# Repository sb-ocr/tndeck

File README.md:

# TN Deck

Watch the build video ↓

TN Deck is a tiny handheld cyberdeck built inside an Altoids tin around the Raspberry Pi Compute Module 0. Inspired by projects like the MintyPi and other tin-based builds, it uses custom PCBs, an integrated keyboard, a small display, onboard audio, and battery power.

<sub>⚠️ In these files, R23 was changed to 2.2kΩ to fix the soft-latch issue, and C33 was added to help reset the audio DAC on power-up.</sub>

[![CC BY-NC-SA 4.0][cc-by-nc-sa-shield]][cc-by-nc-sa]

[![CC BY-NC-SA 4.0][cc-by-nc-sa-image]][cc-by-nc-sa]

[cc-by-nc-sa]: http://creativecommons.org/licenses/by-nc-sa/4.0/
[cc-by-nc-sa-image]: https://licensebuttons.net/l/by-nc-sa/4.0/88x31.png
[cc-by-nc-sa-shield]: https://img.shields.io/badge/License-CC%20BY--NC--SA%204.0-lightgrey.svg

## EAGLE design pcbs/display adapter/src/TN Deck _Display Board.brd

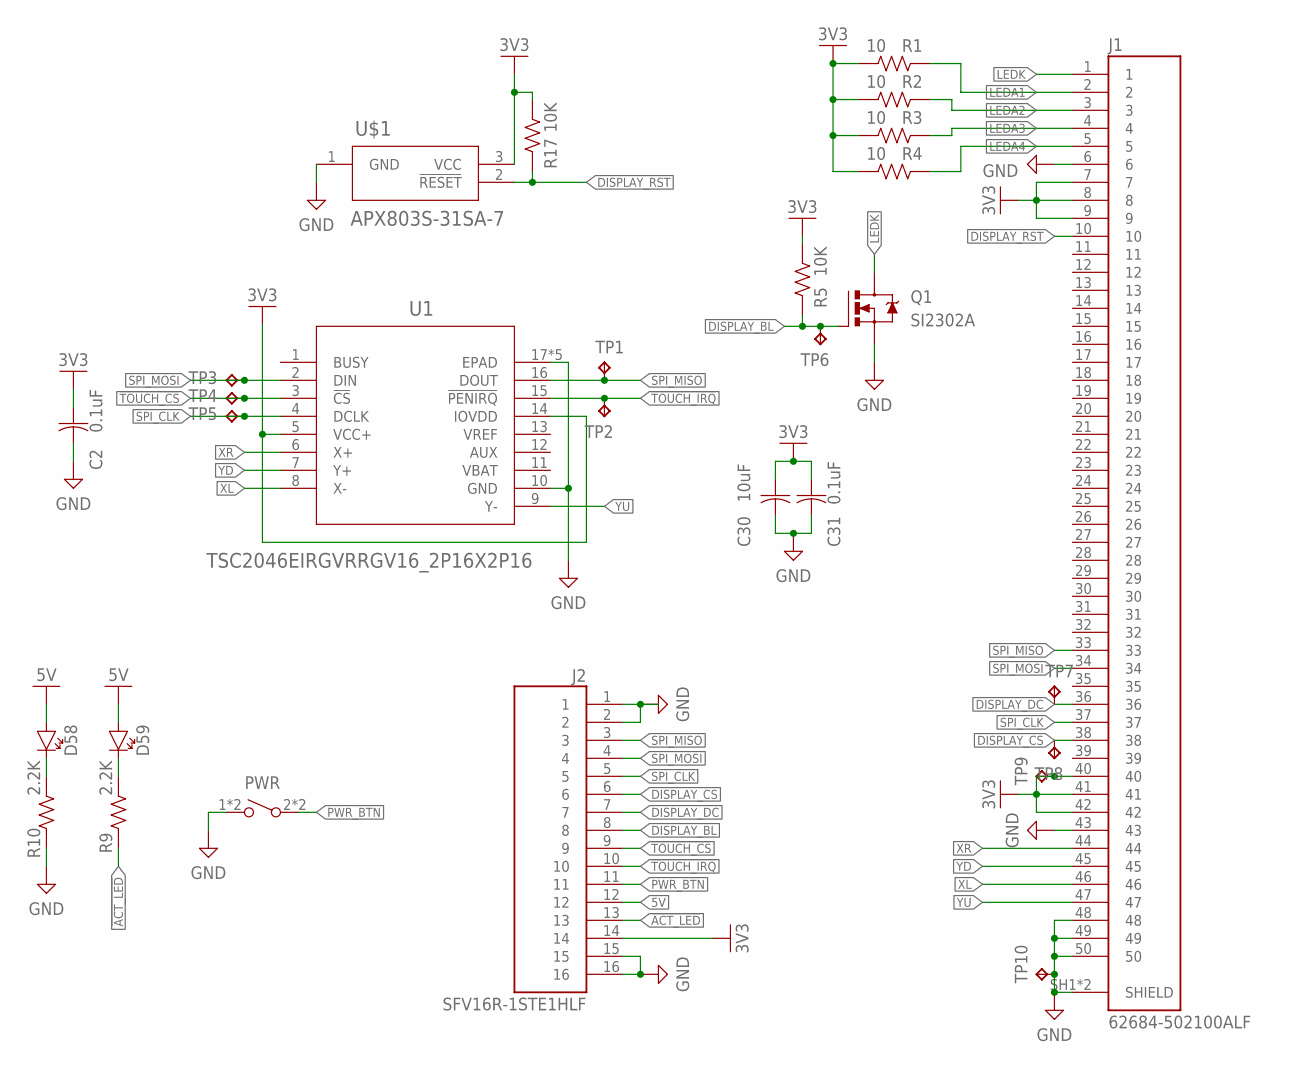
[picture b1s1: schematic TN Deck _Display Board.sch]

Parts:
C2, C31: 0.1uF; CAPC1608X85
C30: 10uF; CAPC2012X110
D58, D59: CHIP-FLAT-G_0603-0.80MM; LEDC1608X80N_FLAT-G
J1: 62684-502100ALF; AMPHENOL_62684-502100ALF
J2: SFV16R-1STE1HLF; AMPHENOL_SFV16R-1STE1HLF
PWR: SPST-NO_SWITCH_KMR2; KMR2
Q1: SI2302A; SOT23
R1, R2, R3, R4: 10; RESC1608X60
R5, R17: 10K; RESC1608X60
R9, R10: 2.2K; RESC1608X60
TP1, TP2, TP3, TP4, TP5, TP6, TP7, TP8, TP9, TP10: TPB1,27; B1,27
U1: TSC2046EIRGVRRGV16_2P16X2P16; RGV16_2P16X2P16
U$1: APX803S-31SA-7; SOT-23_DIO

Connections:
3V3: C2.1, C30.1, C31.1, J1.7, J1.8, J1.9, J1.40, J1.41, J1.42, J2.14, R1.2, R2.2, R3.2, R4.2, R5.2, R17.2, TP9.TP, U1.5 (VCC+), U1.14 (IOVDD), U$1.3 (VCC)
5V: D58.A, D59.A, J2.12
!ACT_LED: J2.13, R9.1
!TOUCH_CS: J2.9, TP4.TP, U1.3 (!CS)
!TOUCH_IRQ: J2.10, TP2.TP, U1.15 (!PENIRQ)
DISPLAY_BL: J2.8, Q1.1 (G), R5.1, TP6.TP
DISPLAY_CS: J1.38, J2.6, TP8.TP
DISPLAY_DC: J1.36, J2.7, TP7.TP
DISPLAY_RST: J1.10, R17.1, U$1.2 (!RESET)
GND: C2.2, C30.2, C31.2, J1.6, J1.43, J1.48, J1.49, J1.50, J1.SH1 (SHIELD), J1.SH2 (SHIELD), J2.1, J2.2, J2.15, J2.16, PWR.1, PWR.4 (1), Q1.2 (S), R10.1, TP10.TP, U1.10 (GND), U1.17 (EPAD), U1.V (EPAD), U1.V_1 (EPAD), U1.V_2 (EPAD), U1.V_3 (EPAD), U$1.1 (GND)
LEDA1: J1.2, R1.1
LEDA2: J1.3, R2.1
LEDA3: J1.4, R3.1
LEDA4: J1.5, R4.1
LEDK: J1.1, Q1.3 (D)
unnamed: D59.C, R9.2
unnamed: D58.C, R10.2
PWR_BTN: J2.11, PWR.2, PWR.3 (2)
SPI_CLK: J1.37, J2.5, TP5.TP, U1.4 (DCLK)
SPI_MISO: J1.33, J2.3, TP1.TP, U1.16 (DOUT)
SPI_MOSI: J1.34, J2.4, TP3.TP, U1.2 (DIN)
VREF: U1.13 (VREF)
XL: J1.46, U1.8 (X-)
XR: J1.44, U1.6 (X+)
YD: J1.45, U1.7 (Y+)
YU: J1.47, U1.9 (Y-)

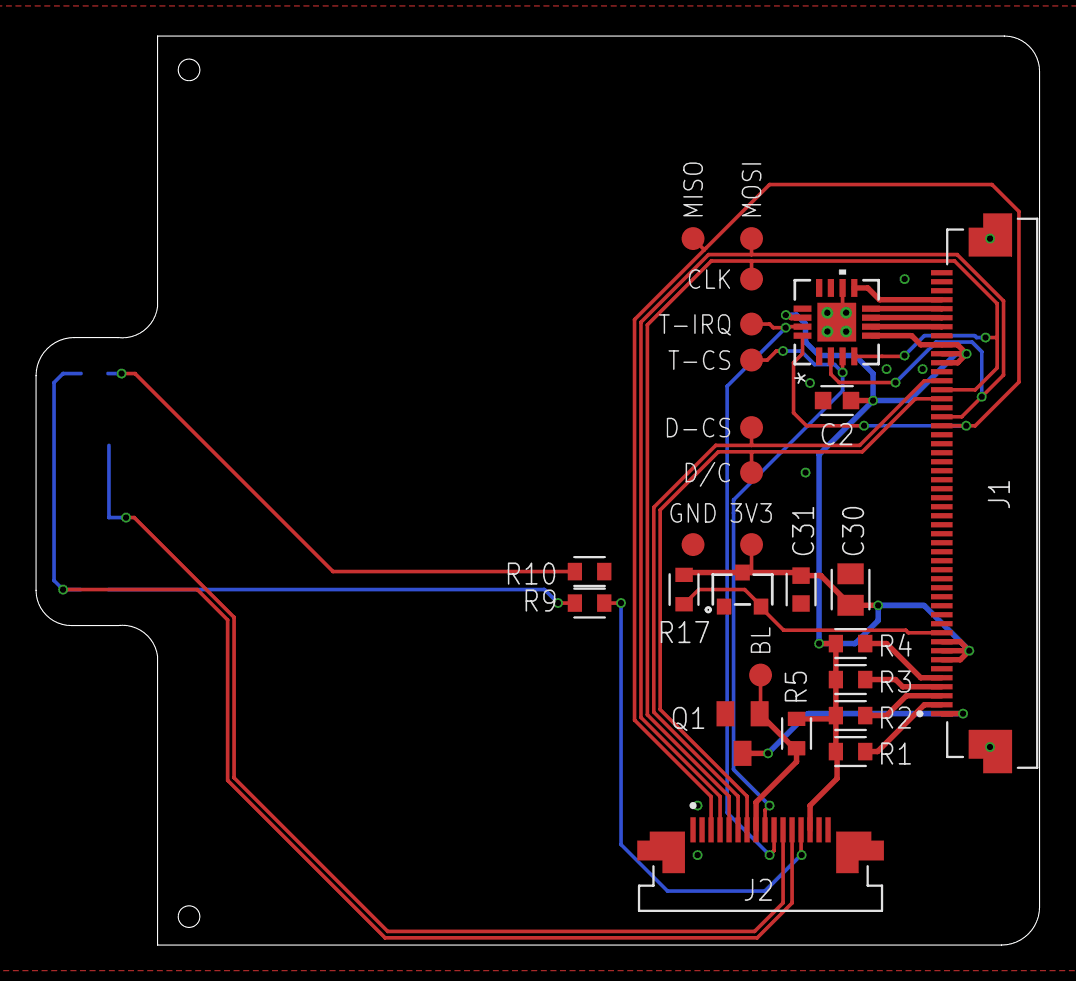
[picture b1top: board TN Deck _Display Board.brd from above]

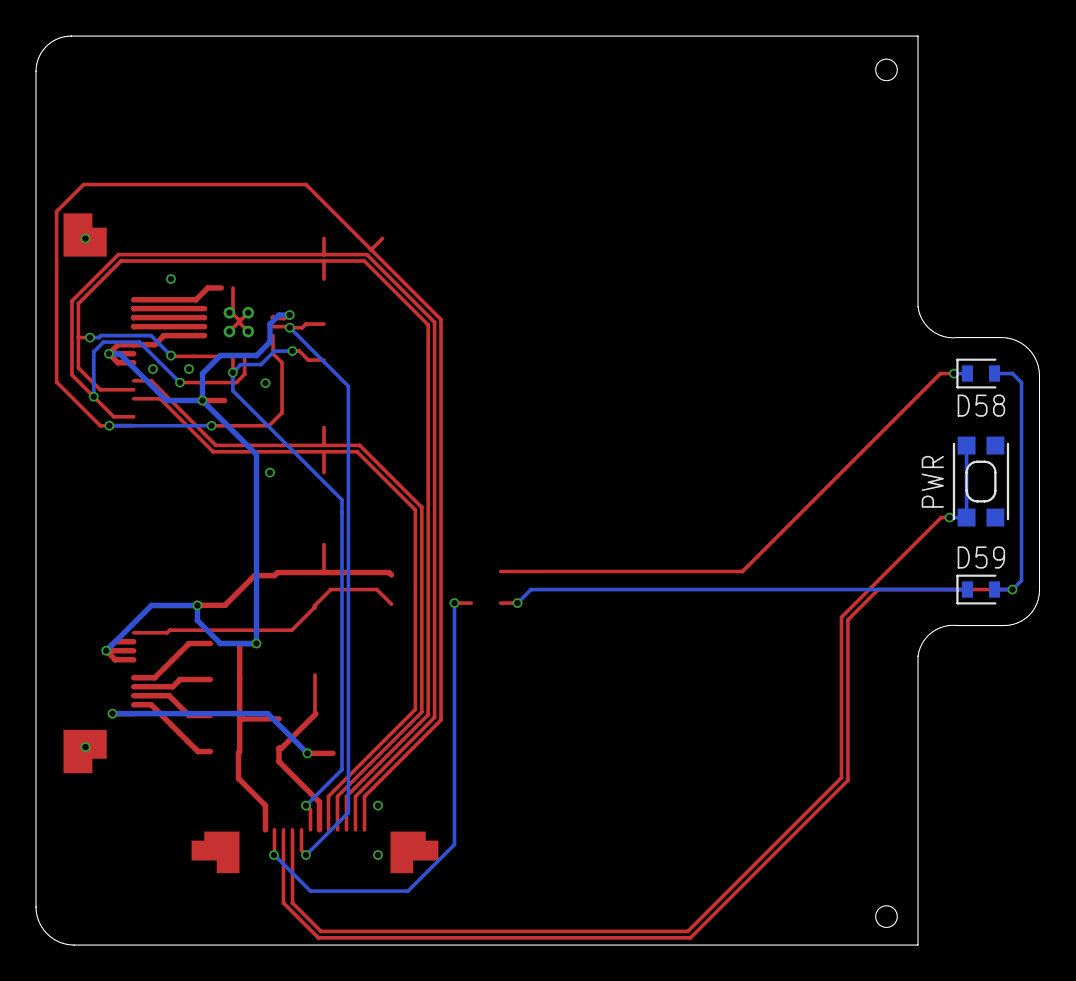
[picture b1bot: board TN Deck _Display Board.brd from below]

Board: 2 copper layers, 55.7 x 50.5 mm, 29 parts (3 on the bottom side), 25 nets.

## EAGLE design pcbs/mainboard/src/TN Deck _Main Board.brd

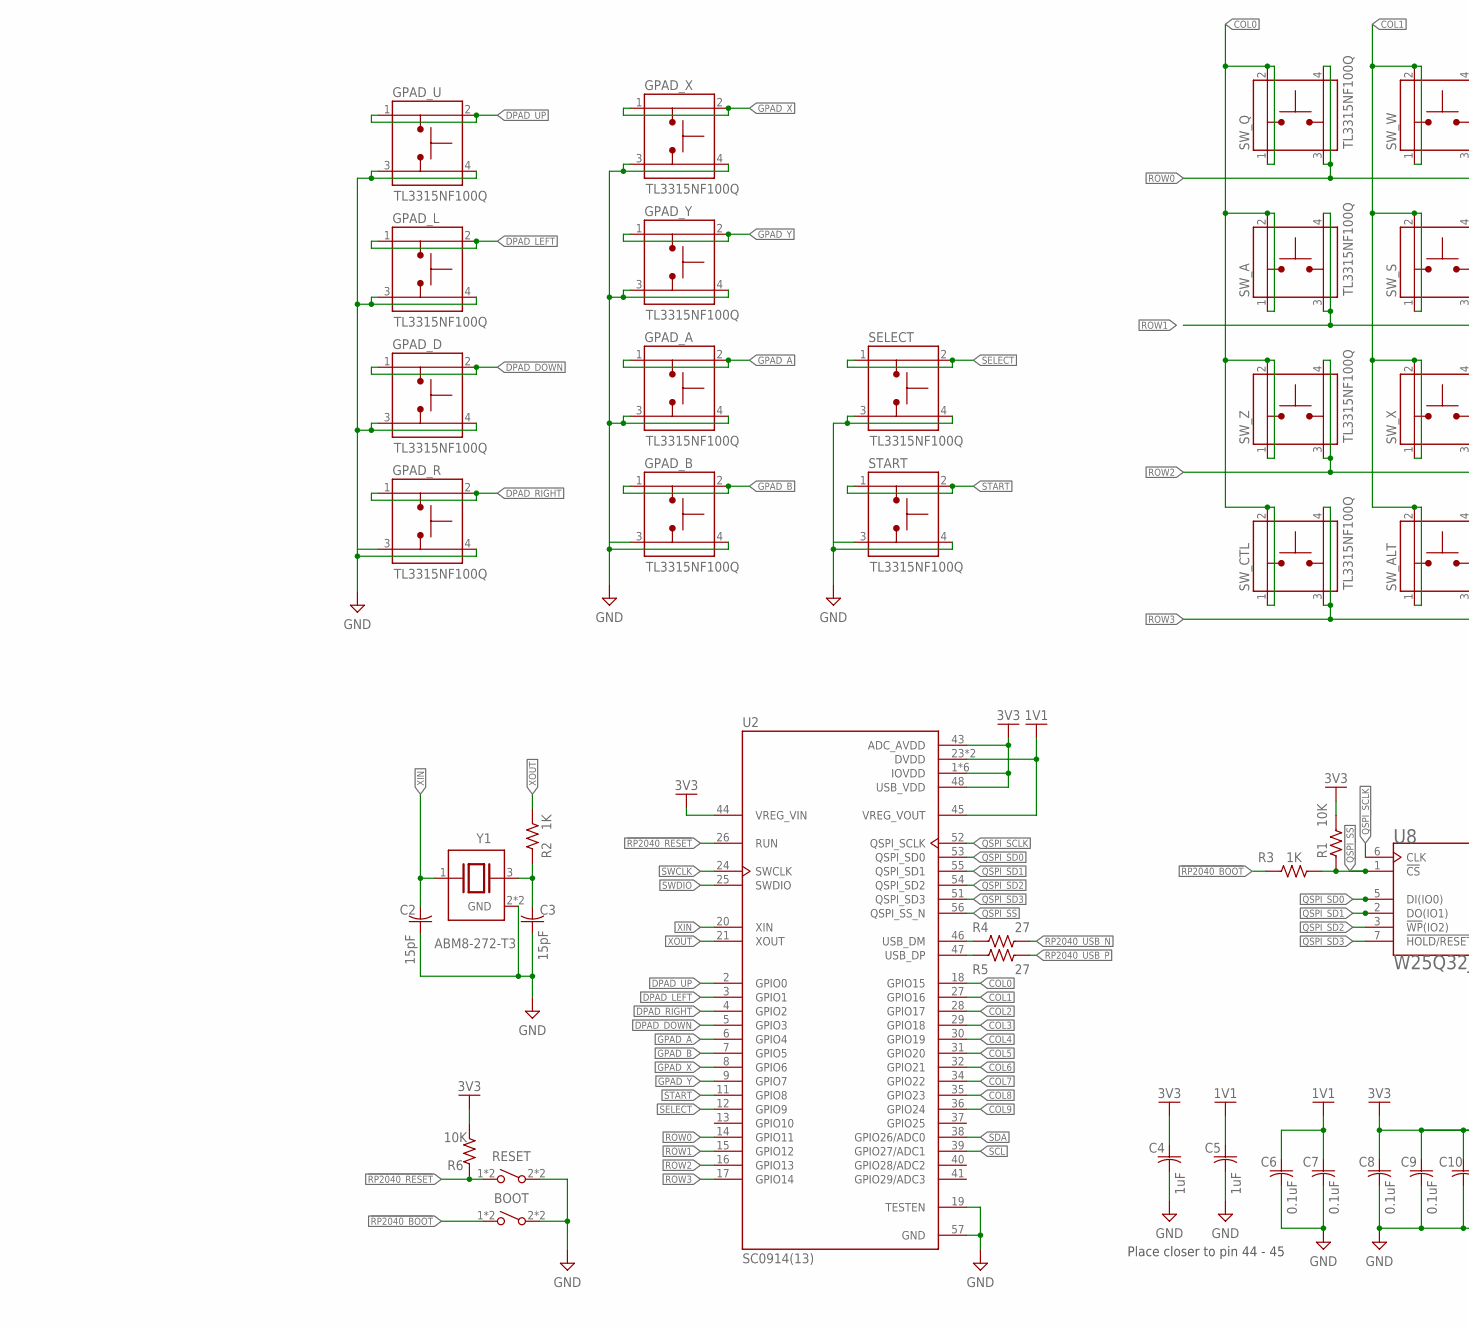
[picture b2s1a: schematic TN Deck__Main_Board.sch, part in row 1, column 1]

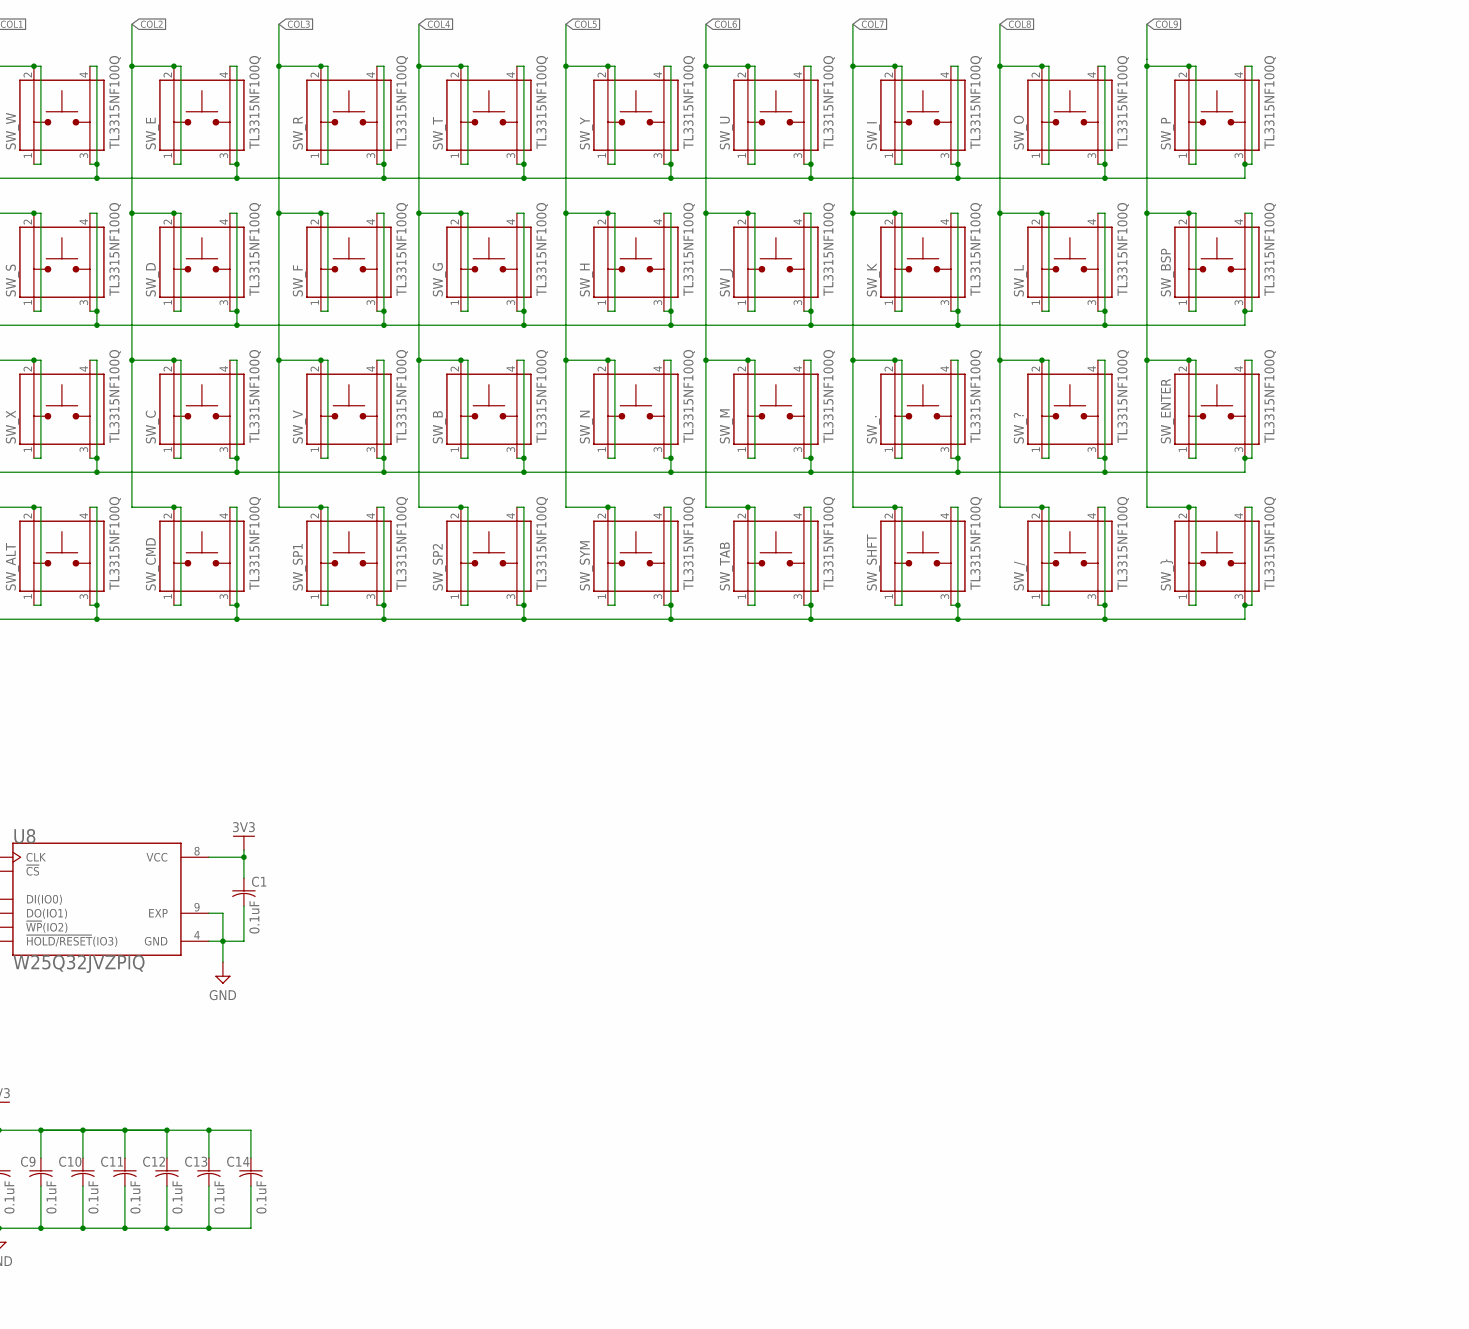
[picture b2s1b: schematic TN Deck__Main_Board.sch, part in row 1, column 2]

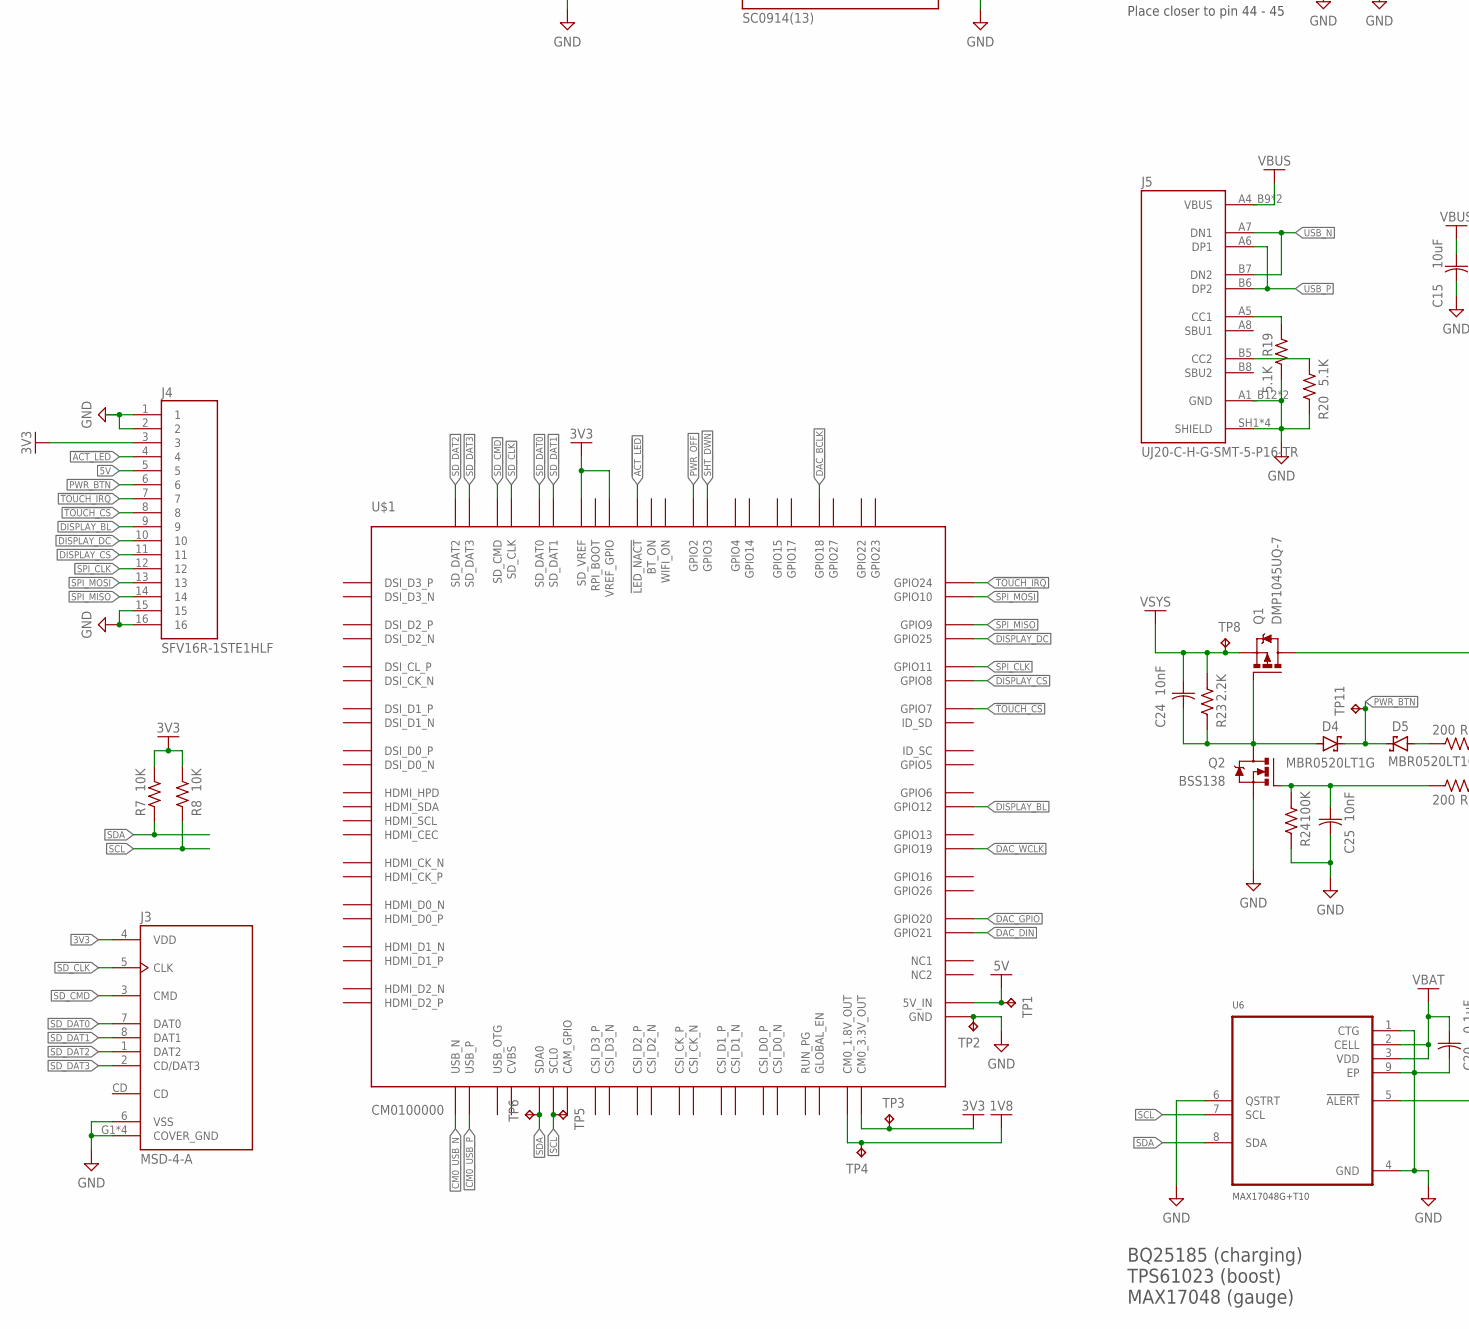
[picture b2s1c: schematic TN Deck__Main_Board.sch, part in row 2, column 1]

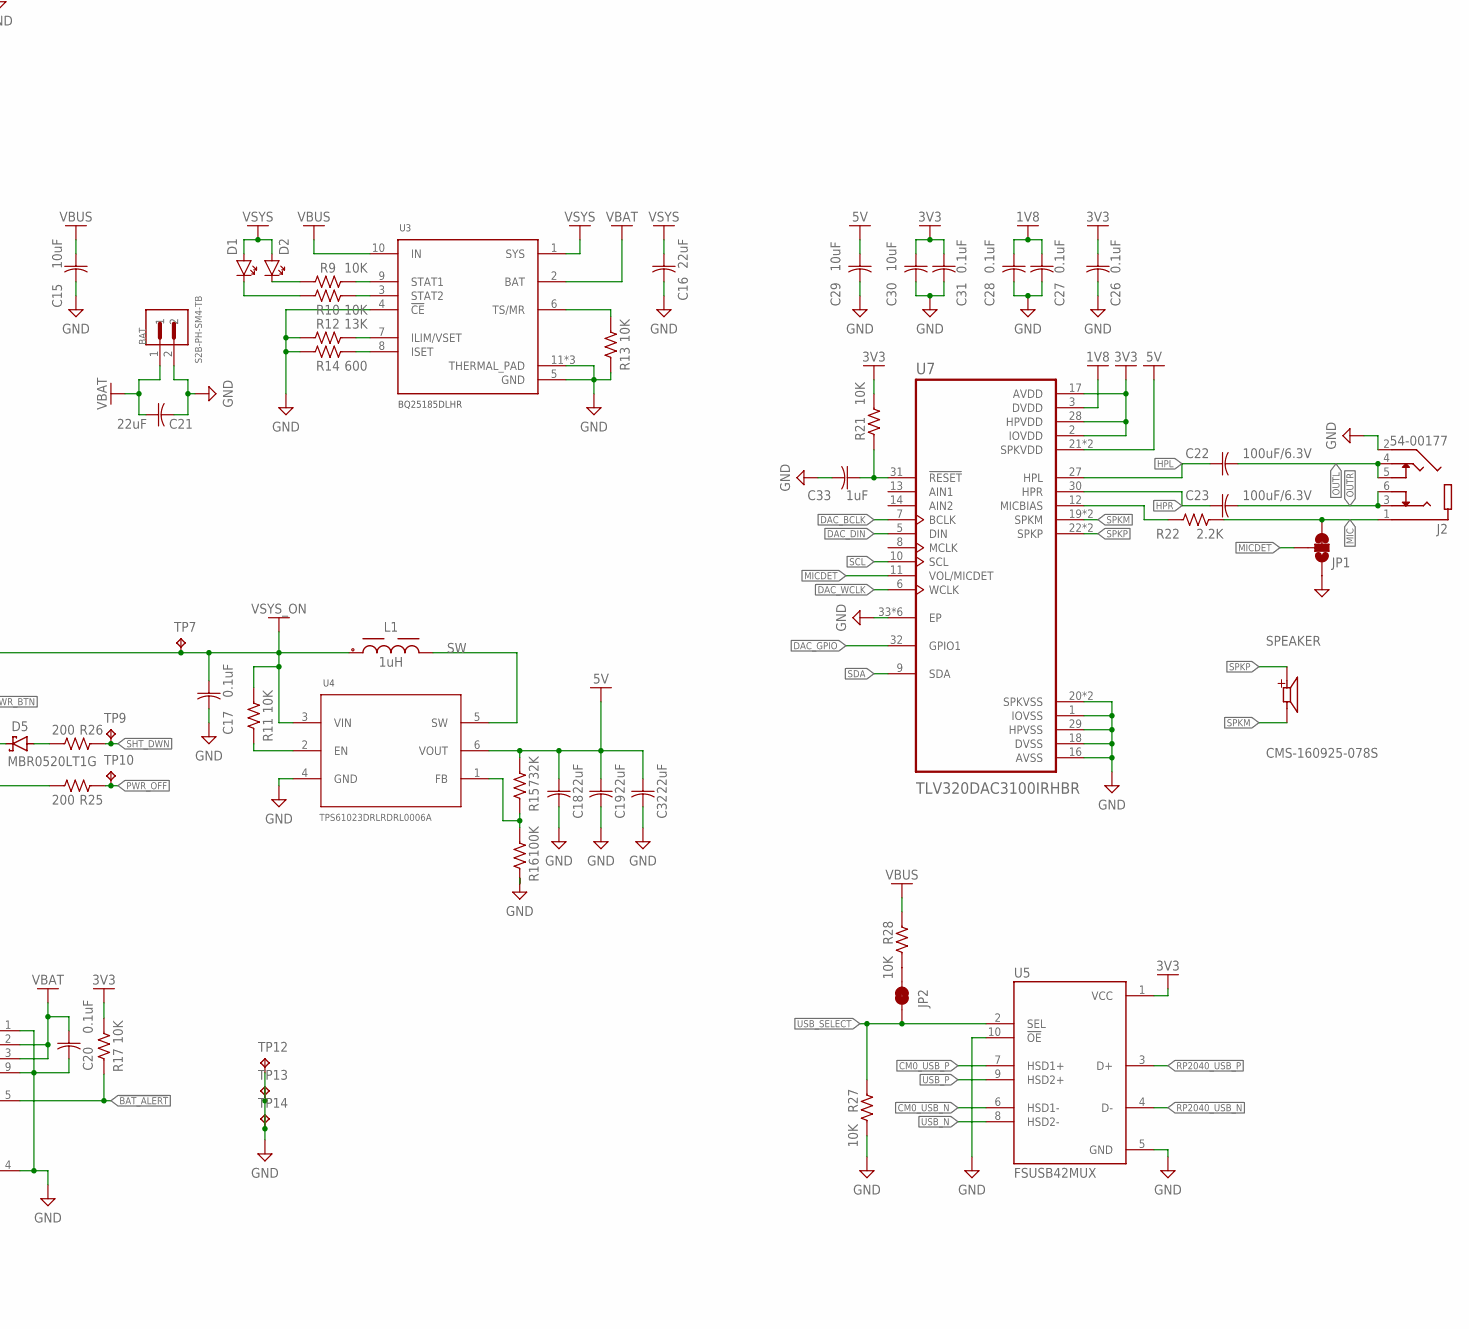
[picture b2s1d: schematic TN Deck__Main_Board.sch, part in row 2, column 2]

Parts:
BAT: S2B-PH-SM4-TB; JST_S2B-PH-SM4-TB
BOOT: SPST-NO_SWITCH_KMR2; KMR2
C1, C6, C7, C8, C9, C10, C11, C12, C13, C14, C17, C20, C26, C27, C28, C31: 0.1uF; CAPC1608X85
C2, C3: 15pF; CAPC1608X85
C4, C5, C33: 1uF; CAPC1608X85
C15, C29, C30: 10uF; CAPC2012X110
C16, C18, C19, C21, C32: 22uF; CAPC2012X110
C22, C23: 100uF/6.3V; CAPC3216X135
C24, C25: 10nF; CAPC1608X85
D1: CHIP-FLAT-G_0603-0.80MM; LEDC1608X80N_FLAT-G
D2: CHIP-FLAT-R_0603-0.80MM; LEDC1608X80N_FLAT-R
D4, D5: MBR0520LT1G; SODFL3718X115
GPAD_A: TL3315NF100Q
GPAD_B: TL3315NF100Q
GPAD_D: TL3315NF100Q
GPAD_L: TL3315NF100Q
GPAD_R: TL3315NF100Q
GPAD_U: TL3315NF100Q
GPAD_X: TL3315NF100Q
GPAD_Y: TL3315NF100Q
J2: 54-00177; TENSILITY_54-00177
J3: MSD-4-A; CUI_MSD-4-A
J4: SFV16R-1STE1HLF; AMPHENOL_SFV16R-1STE1HLF
J5: UJ20-C-H-G-SMT-5-P16-TR; SAMESKY_UJ20-C-H-G-SMT-5-P16-TR
JP1: JUMPER-SMT_3_1-NC_TRACE_SILK; SMT-JUMPER_3_1-NC_TRACE_SILK
JP2: JUMPER-SMT_2_NC_TRACE_NO-SILK; SMT-JUMPER_2_NC_TRACE_NO-SILK
L1: 1uH; WE-XHMI_4020
Q1: DMP1045UQ-7; SOT23
Q2: BSS138; SOT23
R1, R6, R7, R8, R9, R10, R11, R13, R17, R21, R27, R28: 10K; RESC1608X60
R2, R3: 1K; RESC1608X60
R4, R5: 27; RESC1608X60
R12: 13K; RESC1608X60
R14: 600; RESC1608X60
R15: 732K; RESC1608X60
R16, R24: 100K; RESC1608X60
R19, R20: 5.1K; RESC1608X60
R22, R23: 2.2K; RESC1608X60
R25, R26: 200; RESC1608X60
RESET: SPST-NO_SWITCH_KMR2; KMR2
SELECT: TL3315NF100Q
SPEAKER: CMS-160925-078S; SPKR_CMS-160925-078S
START: TL3315NF100Q
SW_.: TL3315NF100Q
SW_/: TL3315NF100Q
SW_?: TL3315NF100Q
SW_A: TL3315NF100Q
SW_ALT: TL3315NF100Q
SW_B: TL3315NF100Q
SW_BSP: TL3315NF100Q
SW_C: TL3315NF100Q
SW_CMD: TL3315NF100Q
SW_CTL: TL3315NF100Q
SW_D: TL3315NF100Q
SW_E: TL3315NF100Q
SW_ENTER: TL3315NF100Q
SW_F: TL3315NF100Q
SW_G: TL3315NF100Q
SW_H: TL3315NF100Q
SW_I: TL3315NF100Q
SW_J: TL3315NF100Q
SW_K: TL3315NF100Q
SW_L: TL3315NF100Q
SW_M: TL3315NF100Q
SW_N: TL3315NF100Q
SW_O: TL3315NF100Q
SW_P: TL3315NF100Q
SW_Q: TL3315NF100Q
SW_R: TL3315NF100Q
SW_S: TL3315NF100Q
SW_SHFT: TL3315NF100Q
SW_SP1, SW_SP2: TL3315NF100Q
SW_SYM: TL3315NF100Q
SW_T: TL3315NF100Q
SW_TAB: TL3315NF100Q
SW_U: TL3315NF100Q
SW_V: TL3315NF100Q
SW_W: TL3315NF100Q
SW_X: TL3315NF100Q
SW_Y: TL3315NF100Q
SW_Z: TL3315NF100Q
SW_}: TL3315NF100Q
TP1, TP2, TP3, TP4, TP5, TP6, TP7, TP8, TP9, TP10, TP11, TP12, TP13, TP14: TPB1,27; B1,27
U2: SC0914(13); QFN40P700X700X90-57N
U3: BQ25185DLHR; IC_BQ25185DLHR
U4: TPS61023DRLRDRL0006A; DRL0006A
U5: FSUSB42MUX; SOP50P490X110-10N
U6: MAX17048G+T10; SON50P200X200X80-9N
U7: TLV320DAC3100IRHBR; IC_ADS125H01IRHBT
U8: W25Q32JVZPIQ; SON127P600X500X80-9N
U$1: CM0100000; CM0
Y1: ABM8-272-T3; XTAL_ABM8-272-T3

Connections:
1V1: C5.1, C6.1, C7.1, U2.23 (DVDD), U2.45 (VREG_VOUT), U2.50 (DVDD)
1V8: C27.1, C28.1, TP4.TP, U7.3 (DVDD), U$1.P$64 (CM0_1.8V_OUT), U$1.P$65 (CM0_1.8V_OUT)
3V3: C1.1, C4.1, C8.1, C9.1, C10.1, C11.1, C12.1, C13.1, C14.1, C26.1, C30.1, C31.1, J3.4 (VDD), J4.3, R1.2, R6.2, R7.2, R8.2, R17.2, R21.2, TP3.TP, U2.1 (IOVDD), U2.10 (IOVDD), U2.22 (IOVDD), U2.33 (IOVDD), U2.42 (IOVDD), U2.43 (ADC_AVDD), U2.44 (VREG_VIN), U2.48 (USB_VDD), U2.49 (IOVDD), U5.1 (VCC), U7.2 (IOVDD), U7.17 (AVDD), U7.28 (HPVDD), U8.8 (VCC), U$1.P$41 (CM0_3.3V_OUT), U$1.P$119 (CM0_3.3V_OUT), U$1.P$120 (VREF_GPIO), U$1.P$122 (SD_VREF)
5V: C18.1, C19.1, C29.1, C32.1, J4.5, R15.2, TP1.TP, U4.6 (VOUT), U7.21 (SPKVDD), U7.24 (SPKVDD), U$1.P$67 (5V_IN), U$1.P$68 (5V_IN)
!ACT_LED: J4.4, U$1.P$118 (!LED_NACT)
!BAT_ALERT: R17.1, U6.5 (!ALERT)
!RP2040_BOOT: BOOT.1, BOOT.4 (1), R3.1
!RP2040_RESET: R6.1, RESET.1, RESET.4 (1), U2.26 (RUN)
!TOUCH_CS: J4.8, U$1.P$89 (GPIO7)
!TOUCH_IRQ: J4.7, U$1.P$98 (GPIO24)
CM0_USB_N: U5.6 (HSD1-), U$1.P$35 (USB_N)
CM0_USB_P: U5.7 (HSD1+), U$1.P$36 (USB_P)
COL0: SW_A.1, SW_A.2, SW_CTL.1, SW_CTL.2, SW_Q.1, SW_Q.2, SW_Z.1, SW_Z.2, U2.18 (GPIO15)
COL1: SW_ALT.1, SW_ALT.2, SW_S.1, SW_S.2, SW_W.1, SW_W.2, SW_X.1, SW_X.2, U2.27 (GPIO16)
COL2: SW_C.1, SW_C.2, SW_CMD.1, SW_CMD.2, SW_D.1, SW_D.2, SW_E.1, SW_E.2, U2.28 (GPIO17)
COL3: SW_F.1, SW_F.2, SW_R.1, SW_R.2, SW_SP1.1, SW_SP1.2, SW_V.1, SW_V.2, U2.29 (GPIO18)
COL4: SW_B.1, SW_B.2, SW_G.1, SW_G.2, SW_SP2.1, SW_SP2.2, SW_T.1, SW_T.2, U2.30 (GPIO19)
COL5: SW_H.1, SW_H.2, SW_N.1, SW_N.2, SW_SYM.1, SW_SYM.2, SW_Y.1, SW_Y.2, U2.31 (GPIO20)
COL6: SW_J.1, SW_J.2, SW_M.1, SW_M.2, SW_TAB.1, SW_TAB.2, SW_U.1, SW_U.2, U2.32 (GPIO21)
COL7: SW_..1, SW_..2, SW_I.1, SW_I.2, SW_K.1, SW_K.2, SW_SHFT.1, SW_SHFT.2, U2.34 (GPIO22)
COL8: SW_/.1, SW_/.2, SW_?.1, SW_?.2, SW_L.1, SW_L.2, SW_O.1, SW_O.2, U2.35 (GPIO23)
COL9: SW_BSP.1, SW_BSP.2, SW_ENTER.1, SW_ENTER.2, SW_P.1, SW_P.2, SW_}.1, SW_}.2, U2.36 (GPIO24)
DAC_BCLK: U7.7 (BCLK), U$1.P$105 (GPIO18)
DAC_DIN: U7.5 (DIN), U$1.P$73 (GPIO21)
DAC_GPIO: U7.32 (GPIO1), U$1.P$74 (GPIO20)
DAC_WCLK: U7.6 (WCLK), U$1.P$79 (GPIO19)
DISPLAY_BL: J4.9, U$1.P$82 (GPIO12)
DISPLAY_CS: J4.11, U$1.P$91 (GPIO8)
DISPLAY_DC: J4.10, U$1.P$94 (GPIO25)
DPAD_DOWN: GPAD_D.1, GPAD_D.2, U2.5 (GPIO3)
DPAD_LEFT: GPAD_L.1, GPAD_L.2, U2.3 (GPIO1)
DPAD_RIGHT: GPAD_R.1, GPAD_R.2, U2.4 (GPIO2)
DPAD_UP: GPAD_U.1, GPAD_U.2, U2.2 (GPIO0)
GND: BAT.2, BOOT.2, BOOT.3 (2), C1.2, C2.1, C3.1, C4.2, C5.2, C6.2, C7.2, C8.2, C9.2, C10.2, C11.2, C12.2, C13.2, C14.2, C15.2, C16.2, C17.2, C18.2, C19.2, C20.2, C21.2, C25.2, C26.2, C27.2, C28.2, C29.2, C30.2, C31.2, C32.2, C33.2, GPAD_A.3, GPAD_A.4, GPAD_B.3, GPAD_B.4, GPAD_D.3, GPAD_D.4, GPAD_L.3, GPAD_L.4, GPAD_R.3, GPAD_R.4, GPAD_U.3, GPAD_U.4, GPAD_X.3, GPAD_X.4, GPAD_Y.3, GPAD_Y.4, J2.2, J3.6 (VSS), J3.G1 (COVER_GND), J3.G2 (COVER_GND), J3.G3 (COVER_GND), J3.G4 (COVER_GND), J4.1, J4.2, J4.15, J4.16, J5.A1_B12 (GND), J5.A12_B1 (GND), J5.SH1 (SHIELD), J5.SH2 (SHIELD), J5.SH3 (SHIELD), J5.SH4 (SHIELD), JP1.1, Q2.2 (S), R12.1, R13.1, R14.1, R16.1, R19.2, R20.1, R24.1, R27.2, RESET.2, RESET.3 (2), SELECT.3, SELECT.4, START.3, START.4, TP2.TP, TP12.TP, TP13.TP, TP14.TP, U2.19 (TESTEN), U2.57 (GND), U3.4 (!CE), U3.5 (GND), U3.11 (THERMAL_PAD), U3.12 (THERMAL_PAD), U3.13 (THERMAL_PAD), U4.4 (GND), U5.5 (GND), U5.10 (!OE), U6.1 (CTG), U6.4 (GND), U6.6 (QSTRT), U6.9 (EP), U7.1 (IOVSS), U7.16 (AVSS), U7.18 (DVSS), U7.20 (SPKVSS), U7.25 (SPKVSS), U7.29 (HPVSS), U7.33 (EP), U7.34 (EP), U7.35 (EP), U7.36 (EP), U7.37 (EP), U7.38 (EP), U8.4 (GND), U8.9 (EXP), U$1.P$1 (GND), U$1.P$4 (GND), U$1.P$7 (GND), U$1.P$10 (GND), U$1.P$13 (GND), U$1.P$16 (GND), U$1.P$21 (GND), U$1.P$24 (GND), U$1.P$27 (GND), U$1.P$30 (GND), U$1.P$33 (GND), U$1.P$34 (GND), U$1.P$37 (GND), U$1.P$40 (GND), U$1.P$45 (GND), U$1.P$48 (GND), U$1.P$51 (GND), U$1.P$54 (GND), U$1.P$57 (GND), U$1.P$60 (GND), U$1.P$63 (GND), U$1.P$66 (GND), U$1.P$69 (GND), U$1.P$72 (GND), U$1.P$75 (GND), U$1.P$78 (GND), U$1.P$81 (GND), U$1.P$84 (GND), U$1.P$87 (GND), U$1.P$90 (GND), U$1.P$93 (GND), U$1.P$96 (GND), U$1.P$99 (GND), U$1.P$100 (GND), U$1.P$103 (GND), U$1.P$106 (GND), U$1.P$109 (GND), U$1.P$112 (GND), U$1.P$115 (GND), U$1.P$123 (GND), U$1.P$126 (GND), U$1.P$129 (GND), U$1.P$132 (GND), Y1.2 (GND), Y1.4 (GND)
GPAD_A: GPAD_A.1, GPAD_A.2, U2.6 (GPIO4)
GPAD_B: GPAD_B.1, GPAD_B.2, U2.7 (GPIO5)
GPAD_X: GPAD_X.1, GPAD_X.2, U2.8 (GPIO6)
GPAD_Y: GPAD_Y.1, GPAD_Y.2, U2.9 (GPIO7)
HPL: C22.1, U7.27 (HPL)
HPR: C23.1, U7.30 (HPR)
MIC: J2.1, JP1.3, R22.2
MICBIAS: R22.1, U7.12 (MICBIAS)
MICDET: JP1.2, U7.11 (VOL/MICDET)
unnamed: R12.2, U3.7 (ILIM/VSET)
unnamed: R14.2, U3.8 (ISET)
unnamed: R13.2, U3.6 (TS/MR)
unnamed: R9.2, U3.9 (STAT1)
unnamed: D2.C, R9.1
unnamed: R10.2, U3.3 (STAT2)
unnamed: D1.C, R10.1
unnamed: R11.1, U4.2 (EN)
unnamed: C3.2, R2.1, Y1.3
unnamed: J5.A5 (CC1), R19.1
unnamed: R15.1, R16.2, U4.1 (FB)
unnamed: J5.B5 (CC2), R20.2
unnamed: C33.1, R21.1, U7.31 (!RESET)
unnamed: C25.1, Q2.1 (G), R24.2, R25.2
unnamed: C24.2, D4.2 (A), Q1.1 (G), Q2.3 (D), R23.1
unnamed: D5.2 (A), R26.2
unnamed: JP2.2, R28.2
OUTL: C22.2, J2.4, J2.5
OUTR: C23.2, J2.3, J2.6
PWR_BTN: D4.1 (C), D5.1 (C), J4.6, TP11.TP
PWR_OFF: R25.1, TP10.TP, U$1.P$114 (GPIO2)
QSPI_SCLK: U2.52 (QSPI_SCLK), U8.6 (CLK)
QSPI_SD0: U2.53 (QSPI_SD0), U8.5 (DI(IO0))
QSPI_SD1: U2.55 (QSPI_SD1), U8.2 (DO(IO1))
QSPI_SD2: U2.54 (QSPI_SD2), U8.3 (!WP!(IO2))
QSPI_SD3: U2.51 (QSPI_SD3), U8.7 (!HOLD/RESET!(IO3))
QSPI_SS: R1.1, R3.2, U2.56 (QSPI_SS_N), U8.1 (!CS)
ROW0: SW_E.3, SW_E.4, SW_I.3, SW_I.4, SW_O.3, SW_O.4, SW_P.3, SW_P.4, SW_Q.3, SW_Q.4, SW_R.3, SW_R.4, SW_T.3, SW_T.4, SW_U.3, SW_U.4, SW_W.3, SW_W.4, SW_Y.3, SW_Y.4, U2.14 (GPIO11)
ROW1: SW_A.3, SW_A.4, SW_BSP.3, SW_BSP.4, SW_D.3, SW_D.4, SW_F.3, SW_F.4, SW_G.3, SW_G.4, SW_H.3, SW_H.4, SW_J.3, SW_J.4, SW_K.3, SW_K.4, SW_L.3, SW_L.4, SW_S.3, SW_S.4, U2.15 (GPIO12)
ROW2: SW_..3, SW_..4, SW_?.3, SW_?.4, SW_B.3, SW_B.4, SW_C.3, SW_C.4, SW_ENTER.3, SW_ENTER.4, SW_M.3, SW_M.4, SW_N.3, SW_N.4, SW_V.3, SW_V.4, SW_X.3, SW_X.4, SW_Z.3, SW_Z.4, U2.16 (GPIO13)
ROW3: SW_/.3, SW_/.4, SW_ALT.3, SW_ALT.4, SW_CMD.3, SW_CMD.4, SW_CTL.3, SW_CTL.4, SW_SHFT.3, SW_SHFT.4, SW_SP1.3, SW_SP1.4, SW_SP2.3, SW_SP2.4, SW_SYM.3, SW_SYM.4, SW_TAB.3, SW_TAB.4, SW_}.3, SW_}.4, U2.17 (GPIO14)
RP2040_USBT_N: R4.1, U2.46 (USB_DM)
RP2040_USBT_P: R5.2, U2.47 (USB_DP)
RP2040_USB_N: R4.2, U5.4 (D-)
RP2040_USB_P: R5.1, U5.3 (D+)
SCL: R8.1, TP5.TP, U2.39 (GPIO27/ADC1), U6.7 (SCL), U7.10 (SCL), U$1.P$43 (SCL0)
SDA: R7.1, TP6.TP, U2.38 (GPIO26/ADC0), U6.8 (SDA), U7.9 (SDA), U$1.P$42 (SDA0)
SD_CLK: J3.5 (CLK), U$1.P$127 (SD_CLK)
SD_CMD: J3.3 (CMD), U$1.P$128 (SD_CMD)
SD_DAT0: J3.7 (DAT0), U$1.P$125 (SD_DAT0)
SD_DAT1: J3.8 (DAT1), U$1.P$124 (SD_DAT1)
SD_DAT2: J3.1 (DAT2), U$1.P$131 (SD_DAT2)
SD_DAT3: J3.2 (CD/DAT3), U$1.P$130 (SD_DAT3)
SELECT: SELECT.1, SELECT.2, U2.12 (GPIO9)
SHT_DWN: R26.1, TP9.TP, U$1.P$113 (GPIO3)
SPI_CLK: J4.12, U$1.P$92 (GPIO11)
SPI_MISO: J4.14, U$1.P$95 (GPIO9)
SPI_MOSI: J4.13, U$1.P$97 (GPIO10)
SPKM: SPEAKER.M, U7.19 (SPKM), U7.23 (SPKM)
SPKP: SPEAKER.P, U7.22 (SPKP), U7.26 (SPKP)
START: START.1, START.2, U2.11 (GPIO8)
SW: L1.2, U4.5 (SW)
SWCLK: U2.24 (SWCLK)
SWDIO: U2.25 (SWDIO)
USB_N: J5.A7 (DN1), J5.B7 (DN2), U5.8 (HSD2-)
USB_P: J5.A6 (DP1), J5.B6 (DP2), U5.9 (HSD2+)
USB_SELECT: JP2.1, R27.1, U5.2 (SEL)
VBAT: BAT.1, C20.1, C21.1, U3.2 (BAT), U6.2 (CELL), U6.3 (VDD)
VBUS: C15.1, J5.A4_B9 (VBUS), J5.B4_A9 (VBUS), R28.1, U3.10 (IN)
VSYS: C16.1, C24.1, D1.A, D2.A, Q1.2 (S), R23.2, TP8.TP, U3.1 (SYS)
VSYS_ON: C17.1, L1.1, Q1.3 (D), R11.2, TP7.TP, U4.3 (VIN)
XIN: C2.2, U2.20 (XIN), Y1.1
XOUT: R2.2, U2.21 (XOUT)

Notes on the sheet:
BQ25185 (charging) TPS61023 (boost) MAX17048 (gauge)
Place closer to pin 44 - 45

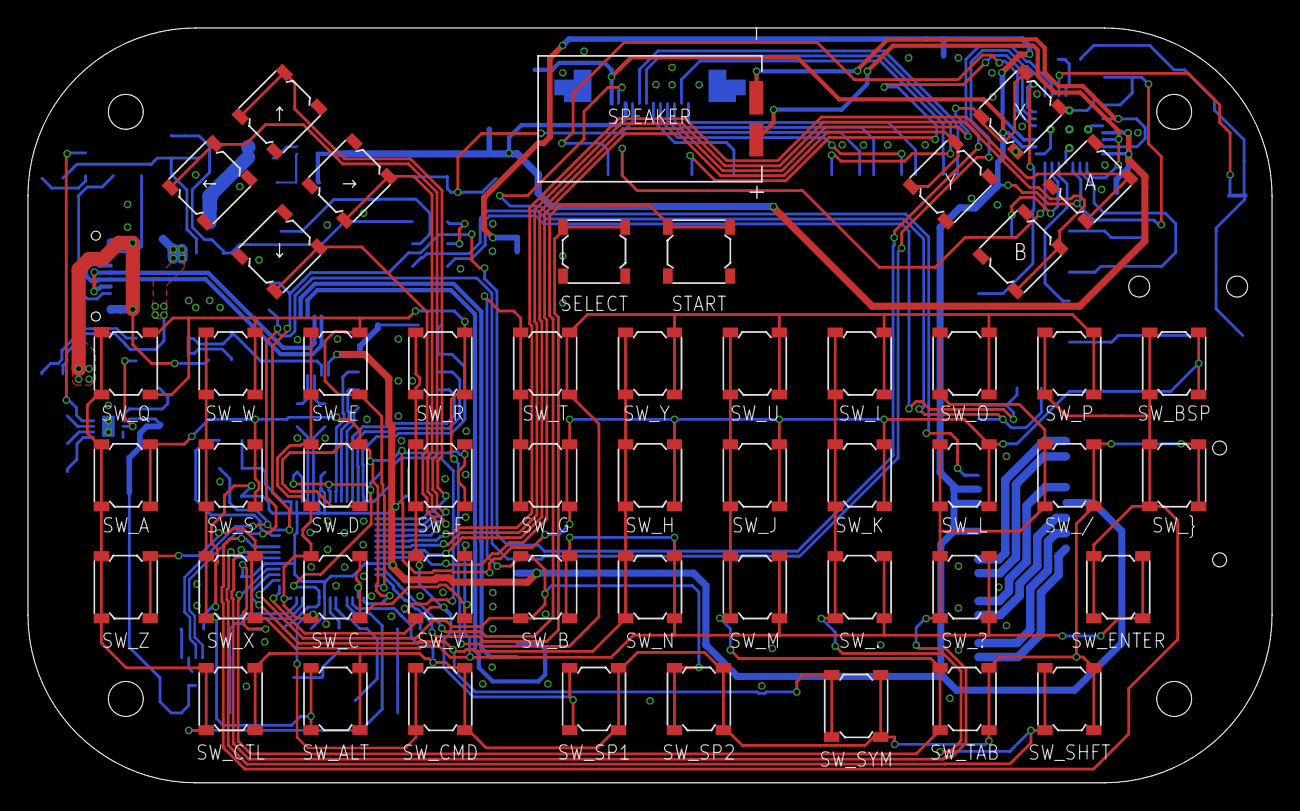
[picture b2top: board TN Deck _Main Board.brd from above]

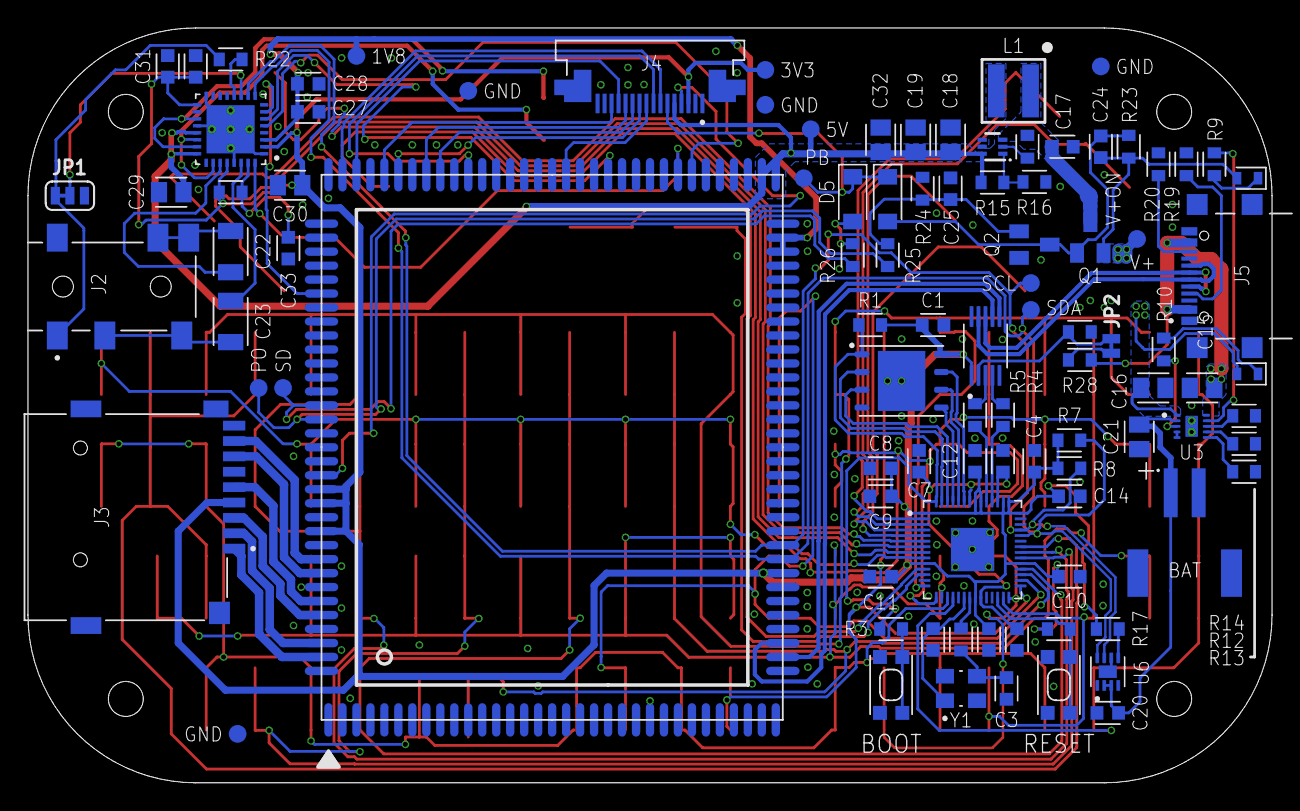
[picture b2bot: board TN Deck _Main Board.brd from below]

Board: 2 copper layers, 89.0 x 54.0 mm, 150 parts (99 on the bottom side), 104 nets.

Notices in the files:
parts and their libraries:
COPYRIGHT: Copyright (C) 2026 Ultra Librarian. All rights reserved.
Wurth_Power Magnetics_WE-XHMI: Copyright: Würth Elektronik
SparkFun-Jumpers: Licensing: Creative Commons ShareAlike 4.0 International - https://creativecommons.org/licenses/by-sa/4.0
